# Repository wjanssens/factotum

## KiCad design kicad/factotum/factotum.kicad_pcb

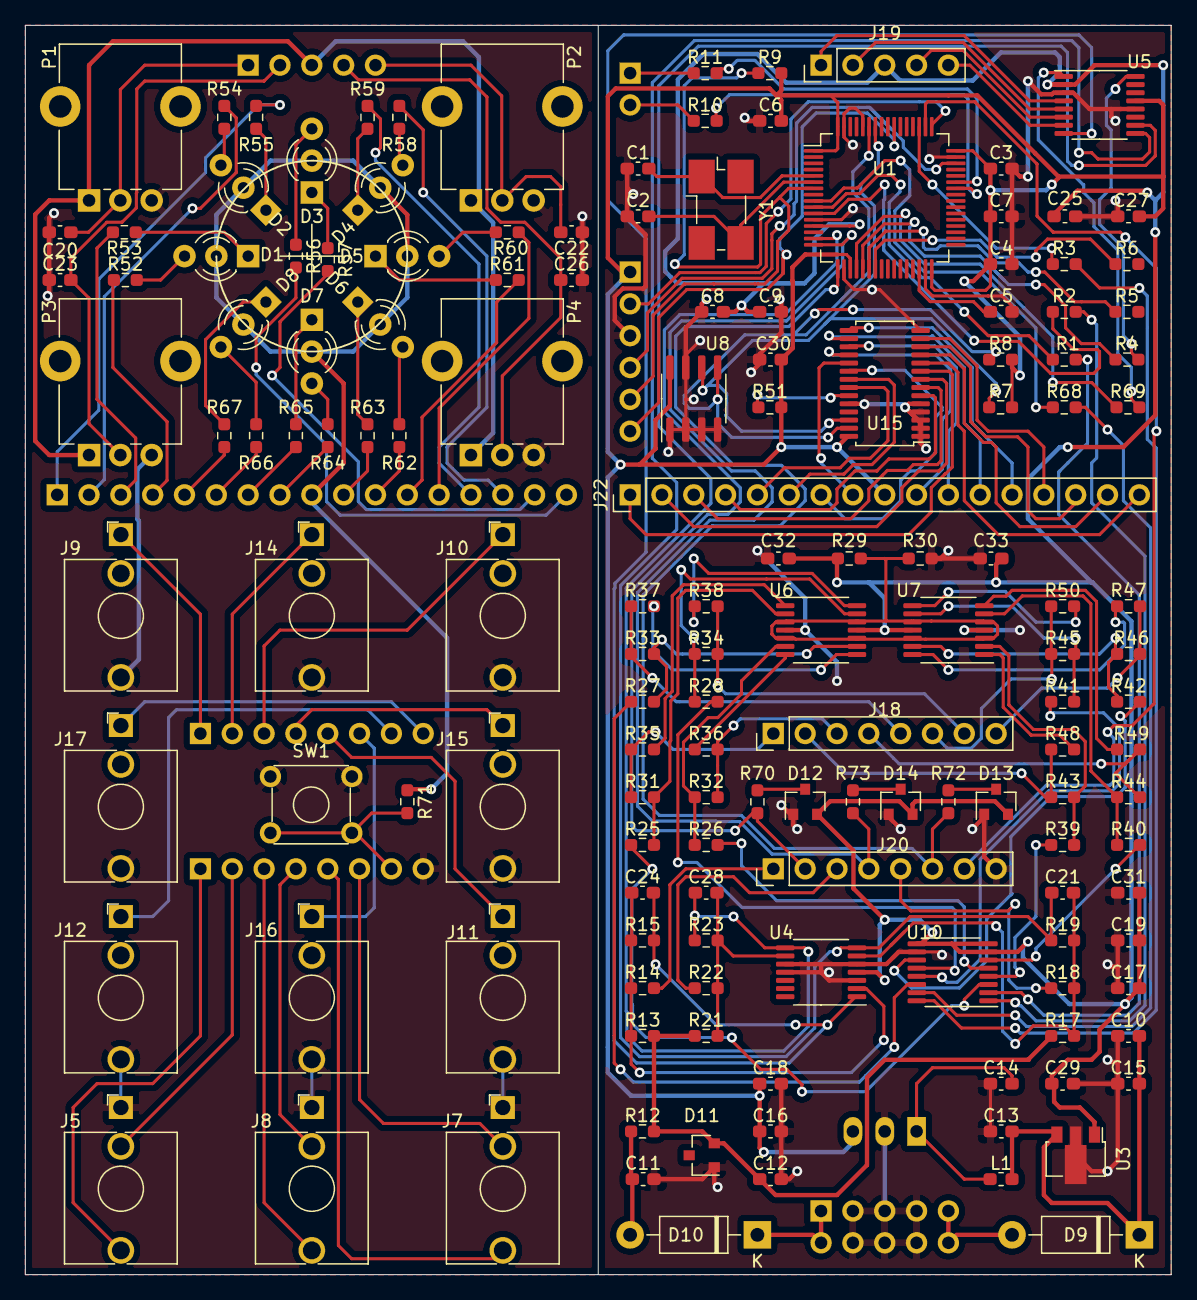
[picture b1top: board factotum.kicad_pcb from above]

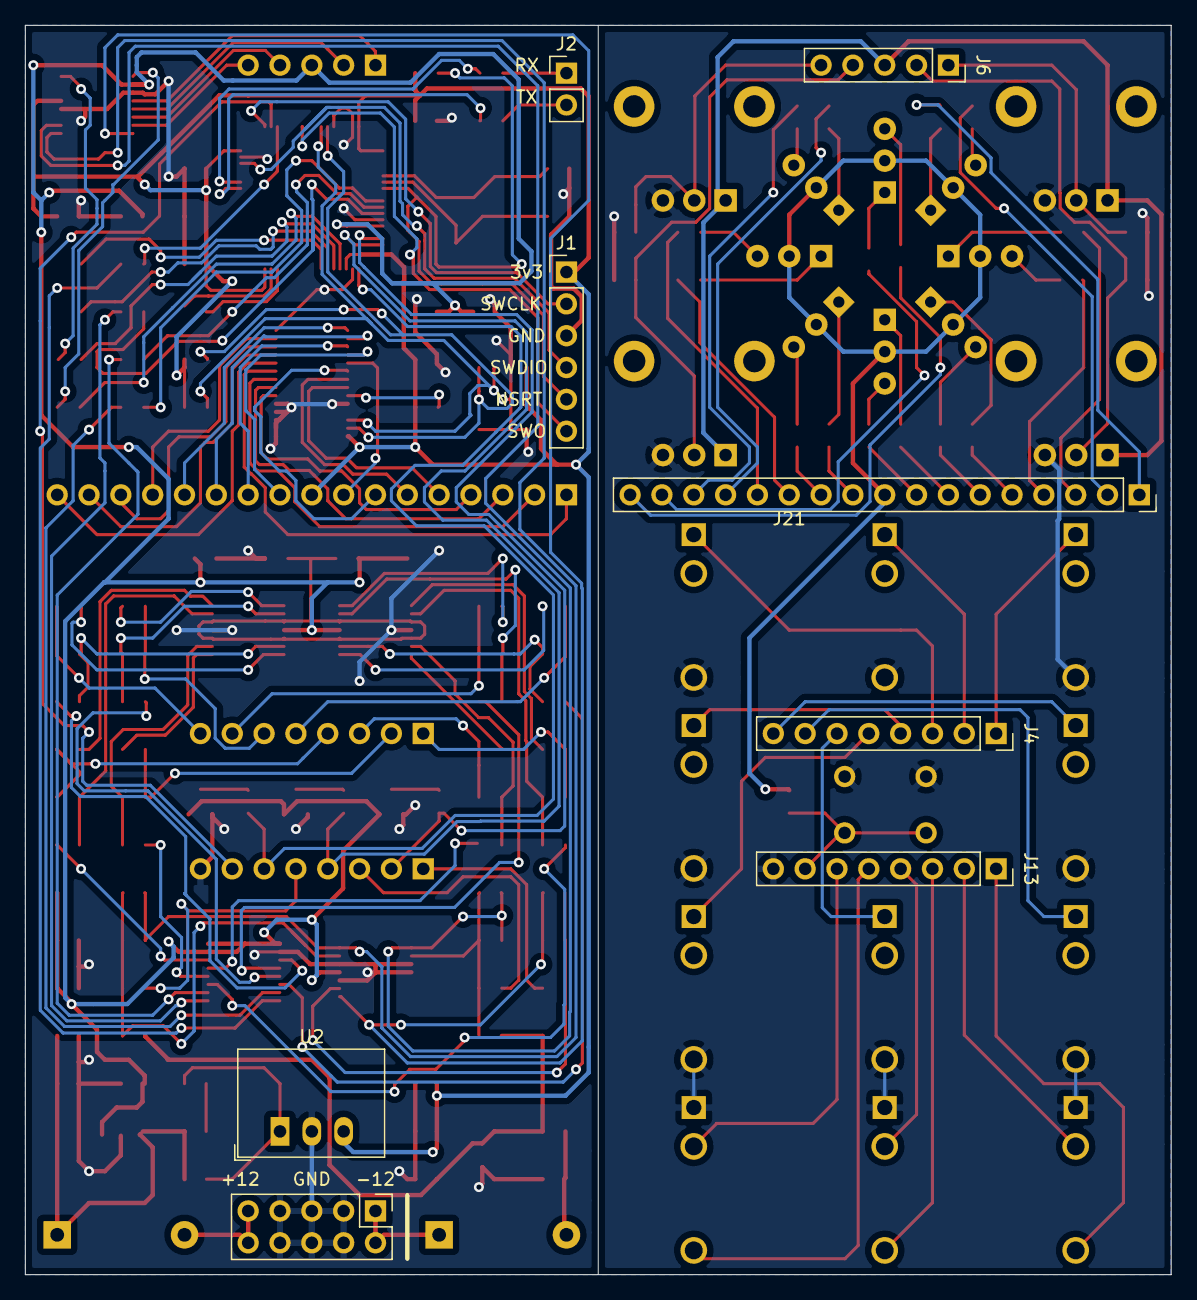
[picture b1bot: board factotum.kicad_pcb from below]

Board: 2 copper layers, 91.4 x 99.7 mm, 156 parts (8 on the bottom side), 159 nets.

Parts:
C1, C2: C_Small; C_0603_1608Metric_Pad1.08x0.95mm_HandSolder
C3, C5, C7, C8, C12: 1u; C_0603_1608Metric_Pad1.08x0.95mm_HandSolder
C4, C6, C9, C16, C25, C27, C29, C30, C31, C32, C33: 100n; C_0603_1608Metric_Pad1.08x0.95mm_HandSolder
C10, C11, C13, C14, C15: 22u; C_0603_1608Metric_Pad1.08x0.95mm_HandSolder
C17, C18, C19: 10u; C_0603_1608Metric_Pad1.08x0.95mm_HandSolder
C20, C22, C23, C26: 33n; C_0603_1608Metric_Pad1.08x0.95mm_HandSolder
C21, C24, C28: 100p; C_0603_1608Metric_Pad1.08x0.95mm_HandSolder
D1, D2, D3, D4, D5, D6, D7, D8: SSL-LX3059IGW-CA; LED_D3.0mm-3
D9, D10: 1N5819; D_DO-41_SOD81_P10.16mm_Horizontal
D11: LM4040B10; SOT-23
D12, D13, D14: BAT54S; SOT-23
J1: Conn_01x06; PinHeader_1x06_P2.54mm_Vertical
J2: USART; PinHeader_1x02_P2.54mm_Vertical
J3: Conn_02x05_Odd_Even; PinHeader_2x05_P2.54mm_Vertical
J4, J13: Conn_01x08_Female; PinSocket_1x08_P2.54mm_Vertical
J5: VOCT; Jack_3.5mm_QingPu_WQP-PJ398SM_Vertical_CircularHoles
J6: Conn_01x05_Female; PinSocket_1x05_P2.54mm_Vertical
J7: RST; Jack_3.5mm_QingPu_WQP-PJ398SM_Vertical_CircularHoles
J8: CLK; Jack_3.5mm_QingPu_WQP-PJ398SM_Vertical_CircularHoles
J9: OUT1; Jack_3.5mm_QingPu_WQP-PJ398SM_Vertical_CircularHoles
J10: OUT3; Jack_3.5mm_QingPu_WQP-PJ398SM_Vertical_CircularHoles
J11: OUT5; Jack_3.5mm_QingPu_WQP-PJ398SM_Vertical_CircularHoles
J12: OUT7; Jack_3.5mm_QingPu_WQP-PJ398SM_Vertical_CircularHoles
J14: OUT2; Jack_3.5mm_QingPu_WQP-PJ398SM_Vertical_CircularHoles
J15: OUT4; Jack_3.5mm_QingPu_WQP-PJ398SM_Vertical_CircularHoles
J16: OUT6; Jack_3.5mm_QingPu_WQP-PJ398SM_Vertical_CircularHoles
J17: OUT8; Jack_3.5mm_QingPu_WQP-PJ398SM_Vertical_CircularHoles
J18, J20: Conn_01x08_Male; PinHeader_1x08_P2.54mm_Vertical
J19: Conn_01x05_Male; PinHeader_1x05_P2.54mm_Vertical
J21: Conn_01x17_Female; PinSocket_1x17_P2.54mm_Vertical
J22: Conn_01x17_Male; PinHeader_1x17_P2.54mm_Vertical
L1: 33u; L_0603_1608Metric_Pad1.05x0.95mm_HandSolder
P1, P2, P3, P4: 10k; Potentiometer_Alpha_RD901F-40-00D_Single_Vertical_CircularH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
R1, R2, R3, R4, R5, R6, R10, R11, R68, R69: 100; R_0603_1608Metric_Pad0.98x0.95mm_HandSolder
R7, R8: 4.7k; R_0603_1608Metric_Pad0.98x0.95mm_HandSolder
R9, R51, R70, R71, R72, R73: 10k; R_0603_1608Metric_Pad0.98x0.95mm_HandSolder
R12: 1.5k; R_0603_1608Metric_Pad0.98x0.95mm_HandSolder
R13, R14, R17, R18, R21, R22: 120k; R_0603_1608Metric_Pad0.98x0.95mm_HandSolder
R15, R19, R23: 20k; R_0603_1608Metric_Pad0.98x0.95mm_HandSolder
R25, R26, R27, R28, R39, R40, R41, R42: 22k; R_0603_1608Metric_Pad0.98x0.95mm_HandSolder
R29: 680k; R_0603_1608Metric_Pad0.98x0.95mm_HandSolder
R30: 510k; R_0603_1608Metric_Pad0.98x0.95mm_HandSolder
R31, R32, R33, R34, R43, R44, R45, R46: 130k; R_0603_1608Metric_Pad0.98x0.95mm_HandSolder
R35, R36, R37, R38, R47, R48, R49, R50: 1k; R_0603_1608Metric_Pad0.98x0.95mm_HandSolder
R52, R54, R56, R58, R60, R62, R64, R66: 68; R_0603_1608Metric_Pad0.98x0.95mm_HandSolder
R53, R55, R57, R59, R61, R63, R65, R67: 56; R_0603_1608Metric_Pad0.98x0.95mm_HandSolder
SW1: MODE_SW; SW_TH_Tactile_Omron_B3F-10xx
U1: STM32F411RETx; LQFP-64_10x10mm_P0.5mm
U2: R-78E3.3-0.5; Converter_DCDC_RECOM_R-78E-0.5_THT
U3: LD2981ABU33; SOT-89-3
U4: MCP6004; TSSOP-14_4.4x5mm_P0.65mm
U5: ADC128S022; TSSOP-16_4.4x5mm_P0.65mm
U6, U7: LM2902; TSSOP-14_4.4x5mm_P0.65mm
U8: M24C02-RMN; SOIC-8_3.9x4.9mm_P1.27mm
U10: DAC128S085; TSSOP-16_4.4x5mm_P0.65mm
U15: PCA9685PW; TSSOP-28_4.4x9.7mm_P0.65mm
Y1: 16 MHz; Crystal_SMD_0603-4Pin_6.0x3.5mm_HandSoldering

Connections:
+3.3VA: C8.1, C9.1, C17.1, C19.1, C25.1, C29.1, C31.1, C32.2, C33.2, D12.2, D13.2, D14.2, J6.3, J19.3, P1.1, P2.1, P3.1, P4.1, R29.1, U1.13, U3.1, U4.4, U5.2, U6.11, U7.11, U10.7, U10.8, U10.9
+3V3: C3.1, C4.1, C6.1, C7.1, C16.1, C18.1, C27.1, C30.1, D1.2, D2.2, D3.2, D4.2, D5.2, D6.2, D7.2, D8.2, J1.1, J21.9, J22.9, R7.2, R8.2, R9.2, R51.2, R71.1, U1.1, U1.19, U1.32, U1.48, U1.64, U2.3, U5.13, U8.8, U15.28
+12V: C10.1, C13.1, C15.1, D9.1, L1.1, U3.3
-10V: C12.1, D11.2, R12.1, R13.2, R17.2, R21.2
-12V: C11.2, D10.2, R12.2
ADC_CLK: C28.2, R23.1, U4.8, U5.10
ADC_CS: R69.1, U5.1
ADC_RST: C21.2, R19.1, U4.7, U5.9
ADC_VOCT: C24.2, R15.1, U4.1, U5.8
B_1: J18.1, R31.1, R35.1
B_2: J18.2, R43.1, R48.1
B_3: J18.3, R32.1, R36.1
B_4: J18.4, R44.1, R49.1
B_5: J18.5, R33.1, R37.1
B_6: J18.6, R45.1, R50.1
B_7: J18.7, R34.1, R38.1
B_8: J18.8, R46.1, R47.1
B_CLK: J20.3, R22.2
B_CLK_SW: J20.4, R73.2, U1.16
B_FRQ: J19.1, U5.4
B_MODE_SW: J20.7, U1.50
B_OFF: J19.2, U5.5
B_RST: J20.5, R18.2
B_RST_SW: J20.6, R72.2, U1.17
B_SCL: J19.4, U5.6
B_SEL: J19.5, U5.7
B_VOCT: J20.1, R14.2
B_VOCT_SW: J20.2, R70.1, U1.15
DAC1: R25.2, U10.3
DAC2: R39.2, U10.4
DAC3: R26.2, U10.5
DAC4: R40.2, U10.6
DAC5: R27.2, U10.14
DAC6: R41.2, U10.13
DAC7: R28.2, U10.12
DAC8: R42.2, U10.11
DAC_SYNC: R68.1, U10.15
G1_B: J22.3, U15.7
G1_T: J21.3, R53.2
G2_B: J22.1, U15.9
G2_T: J21.1, R55.2
G3_B: J22.16, U15.11
G3_T: J21.16, R57.2
G4_B: J22.14, U15.13
G4_T: J21.14, R59.2
G5_B: J22.12, U15.16
G5_T: J21.12, R61.2
G6_B: J22.10, U15.18
G6_T: J21.10, R63.2
G7_B: J22.7, U15.20
G7_T: J21.7, R65.2
G8_B: J22.5, U15.22
G8_T: J21.5, R67.2
GND: C1.2, C2.2, C3.2, C4.2, C5.2, C6.2, C7.2, C8.2, C9.2, C10.2, C11.1, C12.2, C13.2, C14.2, C15.2, C16.2, C17.2, C18.2, C19.2, C20.2, C22.2, C23.2, C25.2, C26.2, C27.2, C29.2, C30.2, C31.2, C32.1, C33.1, D11.1, D12.1, D13.1, D14.1, J1.3, J3.3, J3.4, J3.5, J3.6, J3.7, J3.8, J5.S, J7.S, J8.S, J9.T, J10.T, J11.T, J12.T, J13.8, J14.T, J15.T, J16.T, J17.T, J20.8, P1.3, P2.3, P3.3, P4.3, R30.2, SW1.1, SW1.2, U1.12, U1.18, U1.31, U1.47, U1.60, U1.63, U2.2, U3.2, U4.3, U4.5, U4.10, U4.11, U5.3, U5.12, U6.4, U7.4, U8.1, U8.2, U8.3, U8.4, U8.7, U10.10, U15.1, U15.2, U15.3, U15.4, U15.5, U15.14, U15.24
I2C1_SCL: R7.1, U1.58, U8.6, U15.26
I2C1_SDA: R8.1, U1.59, U8.5, U15.27
IN_NEG: D10.1, J3.1, J3.2
IN_POS: D9.2, J3.9, J3.10
NSRT: J1.5, R9.1, U1.7
unnamed: C1.1, U1.5, Y1.1
unnamed: C2.1, U1.6, Y1.3
unnamed: C5.1, U1.30
unnamed: C14.1, L1.2, U2.1
unnamed: C21.1, R17.1, R18.1, R19.2, U4.6
unnamed: C24.1, R13.1, R14.1, R15.2, U4.2
unnamed: C28.1, R21.1, R22.1, R23.2, U4.9
unnamed: D1.1, R53.1
unnamed: D1.3, R52.1
unnamed: D2.1, R55.1
unnamed: D2.3, R54.1
unnamed: D3.1, R57.1
unnamed: D3.3, R56.1
unnamed: D4.1, R59.1
unnamed: D4.3, R58.1
unnamed: D5.1, R61.1
unnamed: D5.3, R60.1
unnamed: D6.1, R63.1
unnamed: D6.3, R62.1
unnamed: D7.1, R65.1
unnamed: D7.3, R64.1
unnamed: D8.1, R67.1
unnamed: D8.3, R66.1
unnamed: D12.3, R70.2
unnamed: D13.3, R72.1
unnamed: D14.3, R73.1
unnamed: J2.1, R11.2
unnamed: J2.2, R10.2
unnamed: R1.2, U1.10
unnamed: R2.2, U1.11
unnamed: R3.2, U1.51
unnamed: R4.2, U1.21
unnamed: R5.2, U1.22
unnamed: R6.2, U1.23
unnamed: R25.1, R31.2, U6.2
unnamed: R26.1, R32.2, U6.6
unnamed: R27.1, R33.2, U6.9
unnamed: R28.1, R34.2, U6.13
unnamed: R35.2, U6.1
unnamed: R36.2, U6.7
unnamed: R37.2, U6.8
unnamed: R38.2, U6.14
unnamed: R39.1, R43.2, U7.2
unnamed: R40.1, R44.2, U7.6
unnamed: R41.1, R45.2, U7.9
unnamed: R42.1, R46.2, U7.13
unnamed: R47.2, U7.14
unnamed: R48.2, U7.1
unnamed: R49.2, U7.7
unnamed: R50.2, U7.8
unnamed: R51.1, U15.23
unnamed: R68.2, U1.9
unnamed: R69.2, U1.20
R1_B: J22.4, U15.6
R1_T: J21.4, R52.2
R2_B: J22.2, U15.8
R2_T: J21.2, R54.2
R3_B: J22.17, U15.10
R3_T: J21.17, R56.2
R4_B: J22.15, U15.12
R4_T: J21.15, R58.2
R5_B: J22.13, U15.15
R5_T: J21.13, R60.2
R6_B: J22.11, U15.17
R6_T: J21.11, R62.2
R7_B: J22.8, U15.19
R7_T: J21.8, R64.2
R8_B: J22.6, U15.21
R8_T: J21.6, R66.2
RX: R11.1, U1.43
SPI1_MISO: R5.1, U5.15
SPI1_MOSI: R6.1, U5.14
SPI1_SCLK: R4.1, U5.16
SPI2_MISO: R1.1, U10.2
SPI2_MOSI: R2.1, U10.1
SPI2_SCLK: R3.1, U10.16
SWCLK: J1.2, U1.49
SWDIO: J1.4, U1.46
SWO: J1.6, U1.55
TX: R10.1, U1.42
T_1: J4.1, J9.S
T_2: J4.2, J14.S
T_3: J4.3, J10.S
T_4: J4.4, J15.S
T_5: J4.5, J11.S
T_6: J4.6, J16.S
T_7: J4.7, J12.S
T_8: J4.8, J17.S
T_CLK: J8.T, J13.3
T_CLK_SW: J8.TN, J13.4
T_FRQ: C20.1, J6.1, P1.2
T_MODE_SW: J13.7, R71.2, SW1.3, SW1.4
T_OFF: C23.1, J6.2, P3.2
T_RST: J7.T, J13.5
T_RST_SW: J7.TN, J13.6
T_SCL: C26.1, J6.4, P4.2
T_SEL: C22.1, J6.5, P2.2
T_VOCT: J5.T, J13.1
T_VOCT_SW: J5.TN, J13.2
VREF: R29.2, R30.1, U6.3, U6.5, U6.10, U6.12, U7.3, U7.5, U7.10, U7.12

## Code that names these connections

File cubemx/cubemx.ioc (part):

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PC3.Mode=Full_Duplex_Master
PA6.Mode=Full_Duplex_Master
PA7.Mode=Full_Duplex_Master
Mcu.UserName=STM32F411RETx
PA10.Mode=Asynchronous
PB10.Mode=Full_Duplex_Master
PH1\ -\ OSC_OUT.Mode=HSE-External-Oscillator
PC2.Signal=SPI2_MISO
PC2.Mode=Full_Duplex_Master
RCC.SYSCLKSource=RCC_SYSCLKSOURCE_PLLCLK
PA9.Mode=Asynchronous
PH0\ -\ OSC_IN.Mode=HSE-External-Oscillator
PH0\ -\ OSC_IN.Signal=RCC_OSC_IN
PA9.Signal=USART1_TX
PB6.Signal=I2C1_SCL
PB6.Mode=I2C
PC3.Signal=SPI2_MOSI
PB10.Signal=SPI2_SCK
PA5.Signal=SPI1_SCK
RCC.HSE_VALUE=16000000
PH1\ -\ OSC_OUT.Signal=RCC_OSC_OUT
board=custom
PB7.Signal=I2C1_SDA
Mcu.Name=STM32F411R(C-E)Tx
RCC.SYSCLKFreq_VALUE=50000000
Mcu.Package=LQFP64
PA6.Signal=SPI1_MISO
PB7.Mode=I2C
PA10.Signal=USART1_RX
PA5.Mode=Full_Duplex_Master
PA7.Signal=SPI1_MOSI

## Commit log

2020-11-24 fixing mouting holes
2020-11-24 minor edits to notes
2020-11-24 initial commit of vcv rack code
2020-11-24 moving svg files into the right place
2020-11-24 layout components so they fit on a 100mm x 45mm pcb
2020-11-24 fixing component coords
2020-11-29 working on schematic
2020-11-29 initial layout of top board
2020-11-29 small move
2020-12-06 inital board layout done but not routed
2020-12-13 adding switches to inputs; fixing resistor components to 603
2020-12-14 layout components again
2021-01-28 working on pcd routing
2021-01-30 more work on routing
2021-01-31 finished routing
